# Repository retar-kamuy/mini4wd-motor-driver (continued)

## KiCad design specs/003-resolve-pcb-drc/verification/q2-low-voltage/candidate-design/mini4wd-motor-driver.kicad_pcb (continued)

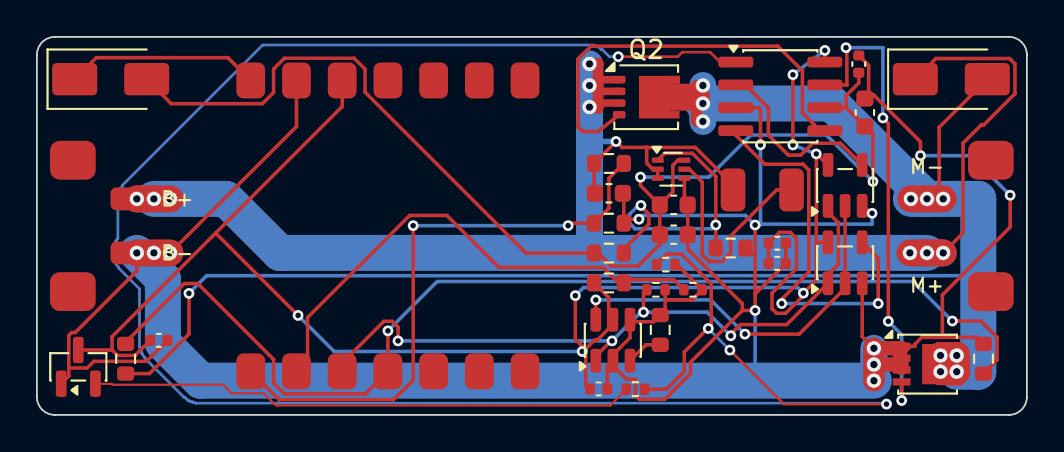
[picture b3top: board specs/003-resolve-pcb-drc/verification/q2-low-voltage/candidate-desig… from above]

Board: 2 copper layers, 55.0 x 21.0 mm, 35 parts (0 on the bottom side), 20 nets.

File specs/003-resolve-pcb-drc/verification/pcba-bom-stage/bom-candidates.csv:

Reference,Qty,Value,Footprint,MPN,Manufacturer,Chosen_Distributor,Datasheet,Validated,DNP,Notes
C1,1,10uF 10V,0603,GRM188R61A106MAALD,Murata,,https://www.murata.com/en-global/api/pdfdownloadapi?cate=luC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,,,
"C2,C3",2,22uF 10V,0603,GRM188R61A226ME15D,Murata,,https://www.murata.com/en-global/api/pdfdownloadapi?cate=luC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,,,
"C101,C102,C103,C104,C106",5,100nF 10V,0402,GRM155R61A104KA01D,Murata,,https://www.murata.com/en-global/api/pdfdownloadapi?cate=luC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,,,
C105,1,2.2uF 16V (candidate),0603,GRM188R61C225KE15D,Murata,,https://www.murata.com/en-global/api/pdfdownloadapi?cate=luC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,,,
D1,1,SS54-HF,SMA_Edge_Assembly,SS54-HF,Comchip Technology,,https://www.comchiptech.com/admin/files/product/20190806165140.pdf,,,
D2,1,SS14-E3,SMA_Edge_Assembly,SS14-E3/61T,Vishay,,https://www.vishay.com/docs/88746/ss12.pdf,,,
J1,1,Micro-Fit 3.0 B+/B-,Molex_MicroFit30_43650-0214,43650-0214,Molex,,https://www.molex.com/content/dam/molex/molex-dot-com/produc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,,,
J2,1,Micro-Fit 3.0 M+/M-,Molex_MicroFit30_43650-0214,43650-0214,Molex,,https://www.molex.com/content/dam/molex/molex-dot-com/produc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,,,
L1,1,1.0uH 9A (XEL4030-102ME),Coilcraft_XEL4030,XEL4030-102MEC,Coilcraft,,https://www.coilcraft.com/en-us/products/power/shielded-indu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,,,
MCU1,1,XIAO MG24 Sense,XIAO_MG24_Castellated_14P,102010610,Seeed Studio,,https://wiki.seeedstudio.com/xiao_mg24_getting_started/,,,
Q1,1,SiSS64DN-T1-GE3,Vishay_PowerPAK_1212-8_Single,SiSS64DN-T1-GE3,Vishay,,https://www.vishay.com/docs/67294/siss64dn.pdf,,,
Q2,1,DMP2008UFG-7,Diodes_PowerDI3333-8_DMP2008UFG,DMP2008UFG-7,Diodes Incorporated,,https://www.diodes.com/datasheet/download/DMP2008UFG.pdf,,,
R1,1,732k 1%,0603,CRCW0603732KFKEA,Vishay,,https://www.vishay.com/docs/20035/dcrcwe3.pdf,,,
R2,1,100k 1%,0603,CRCW0603100KFKEA,Vishay,,https://www.vishay.com/docs/20035/dcrcwe3.pdf,,,
"R3,R5",2,22k 1%,0603,CRCW060322K0FKEA,Vishay,,https://www.vishay.com/docs/20035/dcrcwe3.pdf,,,
"R4,R6,R7",3,10k 1%,0603,CRCW060310K0FKEA,Vishay,,https://www.vishay.com/docs/20035/dcrcwe3.pdf,,,
R101,1,499k 0.5%,0603,RT0603BRD07499KL,Yageo,,https://www.yageogroup.com/content/datasheet/asset/file/pyu-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,,,
R102,1,100k,0402,CRCW0402100KFKED,Vishay,,https://www.vishay.com/docs/20035/dcrcwe3.pdf,,,
R103,1,0 (link),0402,CRCW04020000Z0ED,Vishay,,https://www.vishay.com/docs/20035/dcrcwe3.pdf,,,
R104,1,2.2k 1%,0402,CRCW04022K20FKED,Vishay,,https://www.vishay.com/docs/20035/dcrcwe3.pdf,,,
R105,1,4.7 1%,0402_Gate_NoSilk,CRCW04024R70FKED,Vishay,,https://www.vishay.com/docs/20035/dcrcwe3.pdf,,,SMT assembly only; 1% or better; verify sub-us gate pulse capability; not a current-sense resistor
R106,1,22 1%,0402,CRCW040222R0FKED,Vishay,,https://www.vishay.com/docs/20035/dcrcwe3.pdf,,,SMT assembly only; 1% or better; verify sub-us gate pulse capability; not a current-sense resistor
TH1,1,NTCG104BH103JT1,0402,NTCG104BH103JT1,TDK,,https://product.tdk.com/en/search/sensor/ntc/chip-ntc-thermi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,,,
U2,1,TPS61023DRLR,Texas_R-PDSO-N6_DRL-6,TPS61023DRLR,Texas Instruments,,https://www.ti.com/lit/ds/symlink/tps61023.pdf,,,
U101,1,LTC6994-2 (candidate),TSOT-23-6,LTC6994IS6-2#TRMPBF,Analog Devices,,https://www.analog.com/media/en/technical-documentation/data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,,,
U102,1,SN74LVC1G08DBVR,SOT-23-5,SN74LVC1G08DBVR,Texas Instruments,,https://www.ti.com/lit/ds/symlink/sn74lvc1g08.pdf,,,
U103,1,SN74LVC1G32DBVR,SOT-23-5,SN74LVC1G32DBVR,Texas Instruments,,https://www.ti.com/lit/ds/symlink/sn74lvc1g32.pdf,,,
U104,1,UCC27524ADR (candidate),SOIC-8_3.9x4.9mm_P1.27mm,UCC27524ADR,Texas Instruments,,https://www.ti.com/lit/ds/symlink/ucc27524a.pdf,,,
U105,1,TLV809EA30DBZR (candidate),SOT-23,TLV809EA30DBZR,Texas Instruments,,https://www.ti.com/lit/ds/symlink/tlv803e.pdf,,,
